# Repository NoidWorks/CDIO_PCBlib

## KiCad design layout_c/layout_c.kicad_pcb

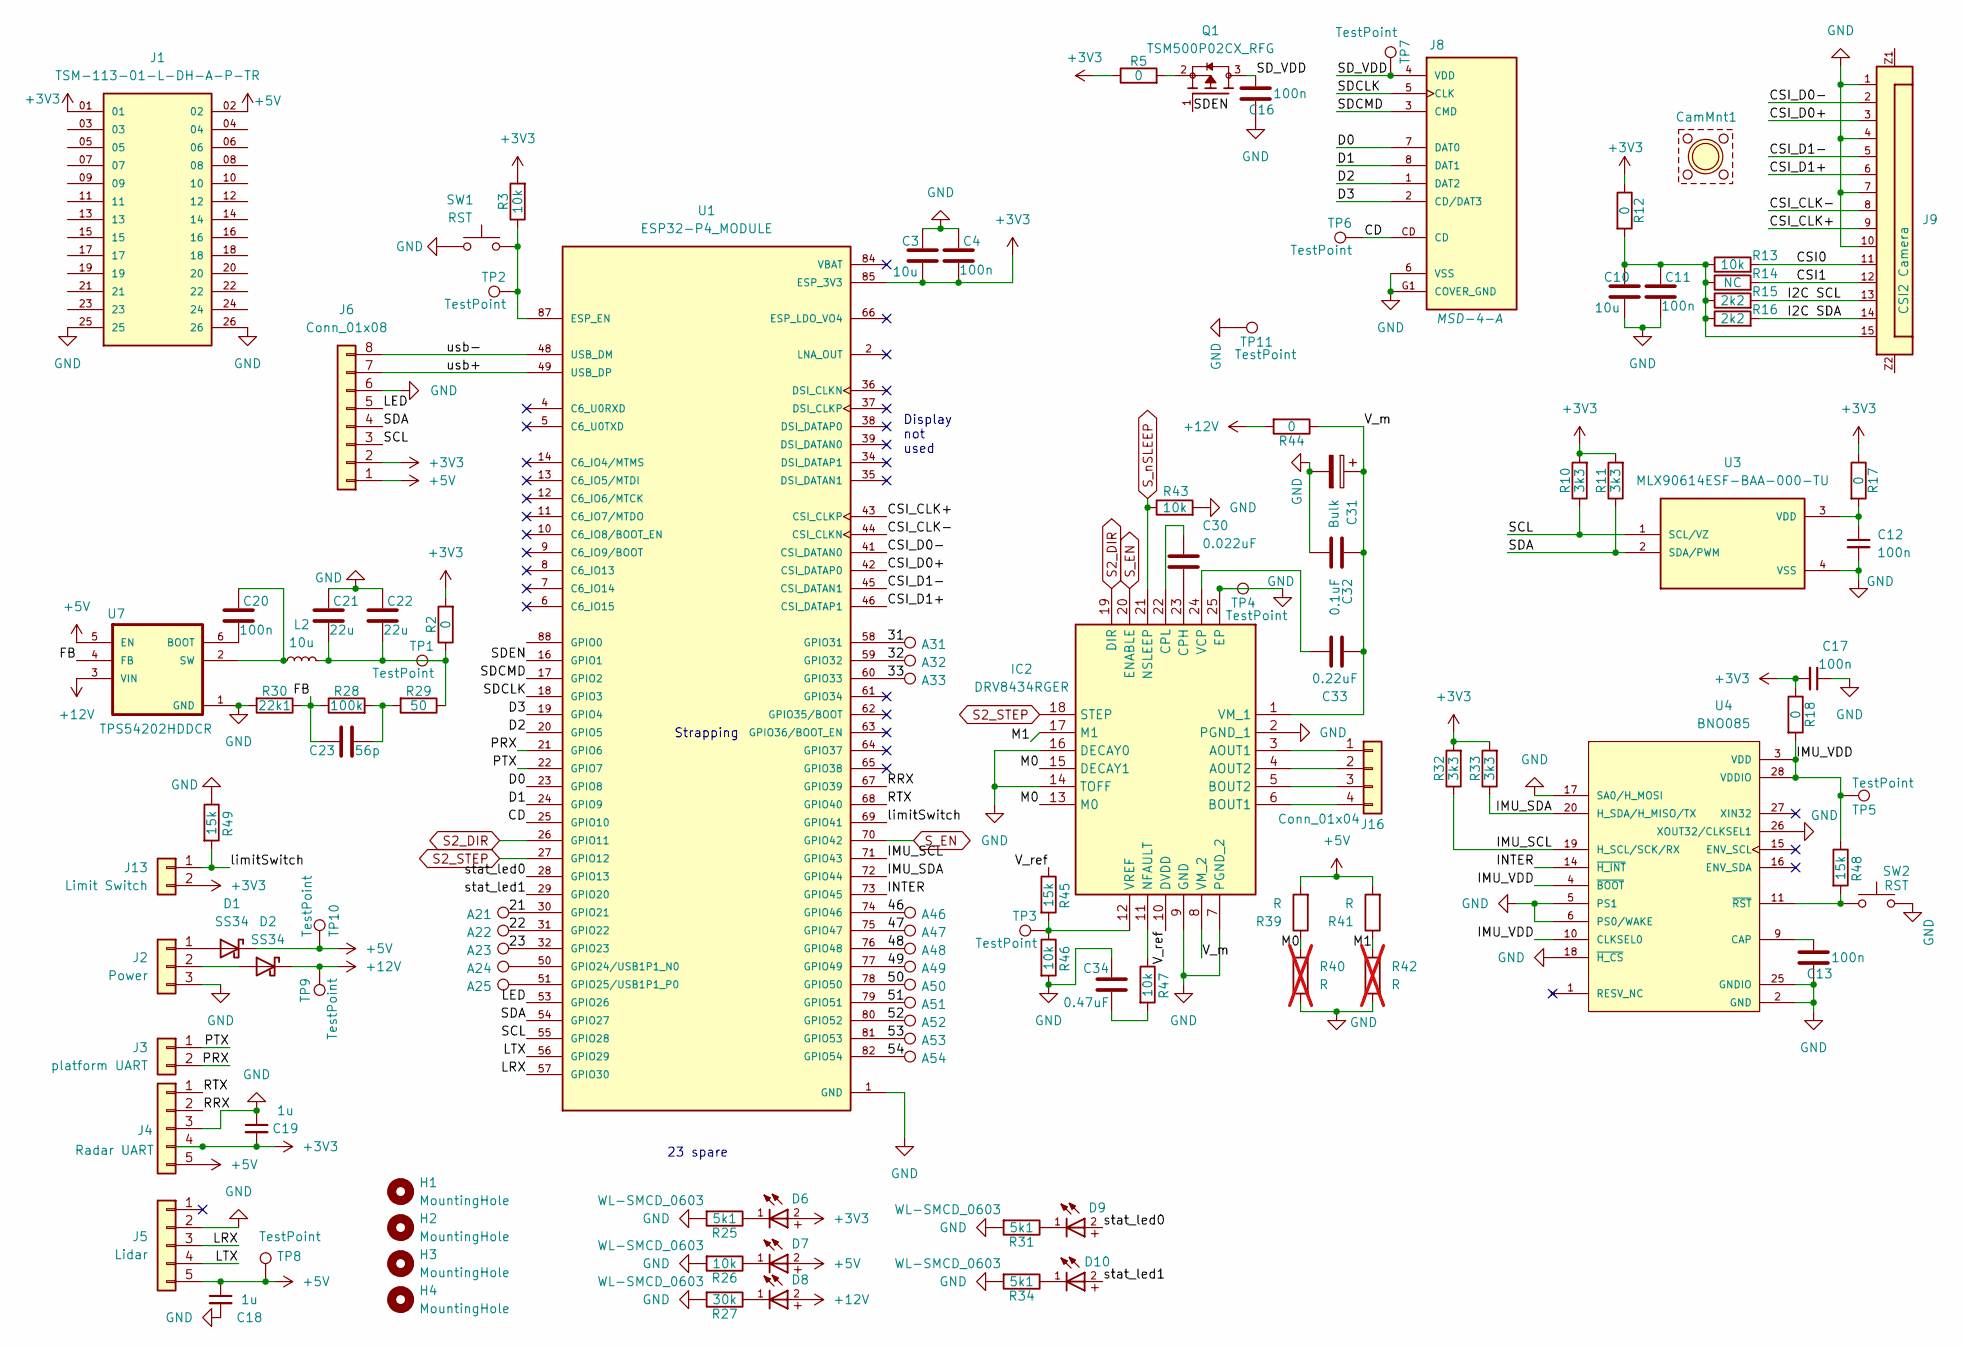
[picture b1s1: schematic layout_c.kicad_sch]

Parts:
A21, A22, A23, A24, A25, A31, A32, A33, A46, A47, A48, A49, A50, A51, A52, A53, A54: Access; TestPoint_Pad_1.5x1.5mm
C3, C10: 10u; C_0805_2012Metric
C4, C11, C12, C13, C16, C17, C20: 100n; C_0805_2012Metric
C18, C19: 1u; C_0805_2012Metric
C21, C22: 22u; C_0805_2012Metric
C23: 56p; C_0805_2012Metric
C30: 0.022uF; C_0402_1005Metric
C31: Bulk; CP_EIA-6032-15_Kemet-U
C32: 0.1uF; C_0402_1005Metric
C33: 0.22uF; C_0402_1005Metric
C34: 0.47uF; C_0402_1005Metric
CamMnt1: PiCamIndicator
D1, D2: SS34; D_SMA
D6, D7, D8, D9, D10: WL-SMCD_0603
H1, H2, H3, H4: MountingHole; MountingHole_3.2mm_M3
IC2: DRV8434RGER; QFN50P400X400X100-25N-D; Mouser Part Number 595-DRV8434RGER
J1: TSM-113-01-L-DH-A-P-TR; SAMTEC_TSM-113-01-L-DH-A-P-TR; PARTREV R
J2: Power; JST_XH_B3B-XH-A_1x03_P2.50mm_Vertical
J3: platform UART; JST_XH_B2B-XH-A_1x02_P2.50mm_Vertical
J4: Radar UART; JST_XH_B5B-XH-A_1x05_P2.50mm_Vertical
J5: Lidar; JST_XH_B5B-XH-A_1x05_P2.50mm_Vertical
J6: Conn_01x08; JST_XH_B8B-XH-A_1x08_P2.50mm_Vertical
J8: MSD-4-A; CUI_MSD-4-A; PARTREV 1.0
J9: CSI2 Camera; 686115183522
J13: Limit Switch; JST_XH_B2B-XH-A_1x02_P2.50mm_Vertical
J16: Conn_01x04; JST_XH_B4B-XH-A_1x04_P2.50mm_Vertical
L2: 10u; L_0805_2012Metric
Q1: TSM500P02CX_RFG; TRANS_TSM500P02CX_RFG; PARTREV C1907
R2, R5, R12, R17, R18, R44: 0; R_0805_2012Metric
R3, R13: 10k; R_0805_2012Metric
R10, R11, R32, R33: 3k3; R_0805_2012Metric
R14: NC; R_0805_2012Metric
R15, R16: 2k2; R_0805_2012Metric
R25, R31, R34: 5k1; R_0603_1608Metric
R26, R43, R46, R47: 10k; R_0603_1608Metric
R27: 30k; R_0603_1608Metric
R28: 100k; R_0603_1608Metric
R29: 50; R_0603_1608Metric
R30: 22k1; R_0603_1608Metric
R39, R41: R; R_0603_1608Metric
R40, R42: R; R_0603_1608Metric; not fitted
R45, R48, R49: 15k; R_0603_1608Metric
SW1, SW2: RST; SW_SPST_CK_RS282G05A3
TP1, TP2, TP3, TP5, TP6, TP7, TP8, TP9, TP10: TestPoint; TestPoint_Pad_D1.0mm
TP4, TP11: TestPoint; TestPoint_Pad_2.5x2.5mm
U1: ESP32-P4_MODULE; XCVR_ESP32-P4_MODULE; PARTREV NA
U3: MLX90614ESF-BAA-000-TU; MLX9061_TO254P942H425-4; PARTREV 13
U4: BNO085; IC_BNO085; PARTREV v1.17
U7: TPS54202HDDCR; SOT95P280X110-6N

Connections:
+3V3: C3.2, C4.2, C17.2, C19.2, D6.2, J1.01, J4.4, J6.2, J13.2, R2.2, R3.2, R5.1, R10.2, R11.2, R12.1, R17.1, R18.1, R32.2, R33.2, U1.85 (ESP_3V3), U1.86 (ESP_3V3)
+5V: C18.1, D1.1 (K), D7.2, J1.02, J4.5, J5.5, J6.1, R39.2, R41.2, TP8.1 (1_1), TP10.1 (1_1), U7.5 (EN)
+12V: D2.1 (K), D8.2, R44.2, TP9.1 (1_1), U7.3 (VIN)
/layout_c/21: A21.1 (1_1), U1.30 (GPIO21)
/layout_c/22: A22.1 (1_1), U1.31 (GPIO22)
/layout_c/23: A23.1 (1_1), U1.32 (GPIO23)
/layout_c/31: A31.1 (1_1), U1.58 (GPIO31)
/layout_c/32: A32.1 (1_1), U1.59 (GPIO32)
/layout_c/33: A33.1 (1_1), U1.60 (GPIO33)
/layout_c/46: A46.1 (1_1), U1.74 (GPIO46)
/layout_c/47: A47.1 (1_1), U1.75 (GPIO47)
/layout_c/48: A48.1 (1_1), U1.76 (GPIO48)
/layout_c/49: A49.1 (1_1), U1.77 (GPIO49)
/layout_c/50: A50.1 (1_1), U1.78 (GPIO50)
/layout_c/51: A51.1 (1_1), U1.79 (GPIO51)
/layout_c/52: A52.1 (1_1), U1.80 (GPIO52)
/layout_c/53: A53.1 (1_1), U1.81 (GPIO53)
/layout_c/54: A54.1 (1_1), U1.82 (GPIO54)
/layout_c/CD: J8.CD, TP6.1 (1_1), U1.25 (GPIO10)
/layout_c/CSI0: J9.11, R13.2
/layout_c/CSI1: J9.12, R14.2
/layout_c/CSI_CLK+: J9.9, U1.43 (CSI_CLKP)
/layout_c/CSI_CLK-: J9.8, U1.44 (CSI_CLKN)
/layout_c/CSI_D0+: J9.3, U1.42 (CSI_DATAP0)
/layout_c/CSI_D0-: J9.2, U1.41 (CSI_DATAN0)
/layout_c/CSI_D1+: J9.6, U1.46 (CSI_DATAP1)
/layout_c/CSI_D1-: J9.5, U1.45 (CSI_DATAN1)
/layout_c/D0: J8.7 (DAT0), U1.23 (GPIO8)
/layout_c/D1: J8.8 (DAT1), U1.24 (GPIO9)
/layout_c/D2: J8.1 (DAT2), U1.20 (GPIO5)
/layout_c/D3: J8.2 (CD/DAT3), U1.19 (GPIO4)
/layout_c/FB: C23.1, R28.1, R30.1, U7.4 (FB)
/layout_c/I2C SCL: J9.13, R15.2
/layout_c/I2C SDA: J9.14, R16.2
/layout_c/IMU_SCL: R32.1, U1.71 (GPIO43), U4.19 (H_SCL/SCK/RX)
/layout_c/IMU_SDA: R33.1, U1.72 (GPIO44), U4.20 (H_SDA/H_MISO/TX)
/layout_c/IMU_VDD: R18.2, R48.1, TP5.1 (1_1), U4.3 (VDD), U4.4 (~BOOT), U4.10 (CLKSEL0), U4.28 (VDDIO)
/layout_c/INTER: U1.73 (GPIO45), U4.14 (~H_INT)
/layout_c/LED: J6.5, U1.53 (GPIO26)
/layout_c/LRX: J5.3, U1.57 (GPIO30)
/layout_c/LTX: J5.4, U1.56 (GPIO29)
/layout_c/M0: IC2.13 (M0), IC2.15 (DECAY1), R39.1, R40.1
/layout_c/M1: IC2.17 (M1), R41.1, R42.1
/layout_c/PRX: J3.2, U1.21 (GPIO6)
/layout_c/PTX: J3.1, U1.22 (GPIO7)
/layout_c/RRX: J4.2, U1.67 (GPIO39)
/layout_c/RTX: J4.1, U1.68 (GPIO40)
/layout_c/SCL: J6.3, R10.1, U1.55 (GPIO28), U3.1 (SCL/VZ)
/layout_c/SDA: J6.4, R11.1, U1.54 (GPIO27), U3.2 (SDA/PWM)
/layout_c/SDCLK: J8.5 (CLK), U1.18 (GPIO3)
/layout_c/SDCMD: J8.3 (CMD), U1.17 (GPIO2)
/layout_c/SDEN: Q1.1, U1.16 (GPIO1)
/layout_c/SD_VDD: C16.2, J8.4 (VDD), Q1.3, TP7.1 (1_1)
/layout_c/V_m: C31.1, C32.1, C33.1, IC2.1 (VM_1), IC2.8 (VM_2), R44.1
/layout_c/V_ref: IC2.10 (DVDD), R45.1
/layout_c/limitSwitch: J13.1, R49.2, U1.69 (GPIO41)
/layout_c/stat_led0: D9.2, U1.28 (GPIO13)
/layout_c/stat_led1: D10.2, U1.29 (GPIO20)
/layout_c/usb+: J6.7, U1.49 (USB_DP)
/layout_c/usb-: J6.8, U1.48 (USB_DM)
GND: C3.1, C4.1, C10.2, C11.2, C12.2, C13.1, C16.1, C17.1, C18.2, C19.1, C21.1, C22.1, C31.2, C32.2, C34.1, IC2.2 (PGND_1), IC2.7 (PGND_2), IC2.9 (GND), IC2.14 (TOFF), IC2.16 (DECAY0), IC2.25 (EP), J1.25, J1.26, J2.3, J4.3, J5.2, J6.6, J8.6 (VSS), J8.G1 (COVER_GND), J8.G2 (COVER_GND), J8.G3 (COVER_GND), J8.G4 (COVER_GND), J9.1, J9.4, J9.7, J9.10, R25.2, R26.2, R27.2, R30.2, R31.2, R34.2, R40.2, R42.2, R43.2, R46.2, R49.1, SW1.1, SW2.2, TP4.1 (1_1), TP11.1 (1_1), U1.1 (GND), U1.3 (GND), U1.15 (GND), U1.33 (GND), U1.40 (GND), U1.47 (GND), U1.52 (GND), U1.83 (GND), U3.4 (VSS), U4.2 (GND), U4.5 (PS1), U4.6 (PS0/WAKE), U4.17 (SA0/H_MOSI), U4.18 (~H_CS), U4.25 (GNDIO), U4.26 (XOUT32/CLKSEL1), U7.1 (GND); also elsewhere on the board
unnamed: C10.1, C11.1, J9.15, R12.2, R13.1, R14.1, R15.1, R16.1
unnamed: C21.2, C22.2, L2.2, R2.1, R29.1, TP1.1 (1_1)
unnamed: C23.2, R28.2, R29.2
unnamed: C34.2, R47.2
unnamed: D1.2 (A), J2.1
unnamed: D2.2 (A), J2.2
unnamed: D6.1, R25.1
unnamed: D7.1, R26.1
unnamed: D8.1, R27.1
unnamed: D9.1, R31.1
unnamed: D10.1, R34.1
unnamed: IC2.3 (AOUT1), J16.1
unnamed: IC2.4 (AOUT2), J16.2
unnamed: IC2.6 (BOUT1), J16.4
unnamed: IC2.5 (BOUT2), J16.3
unnamed: C30.2, IC2.23 (CPH)
unnamed: C30.1, IC2.22 (CPL)
unnamed: IC2.11 (NFAULT), R47.1
unnamed: C33.2, IC2.24 (VCP)
unnamed: IC2.12 (VREF), R45.2, R46.1, TP3.1 (1_1)
unnamed: Q1.2, R5.2
unnamed: R3.1, SW1.2, TP2.1 (1_1), U1.87 (ESP_EN)
unnamed: A24.1 (1_1), U1.50 (GPIO24/USB1P1_N0)
unnamed: A25.1 (1_1), U1.51 (GPIO25/USB1P1_P0)
unnamed: C12.1, R17.2, U3.3 (VDD)
unnamed: C13.2, U4.9 (CAP)
unnamed: R48.2, SW2.1, U4.11 (~RST)
unnamed: C20.2, U7.6 (BOOT)
unnamed: C20.1, L2.1, U7.2 (SW)
S2_DIR: IC2.19 (DIR), U1.26 (GPIO11)
S2_STEP: IC2.18 (STEP), U1.27 (GPIO12)
S_EN: IC2.20 (ENABLE), U1.70 (GPIO42)
S_nSLEEP: IC2.21 (NSLEEP), R43.1

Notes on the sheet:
Display not used
23 spare
Strapping

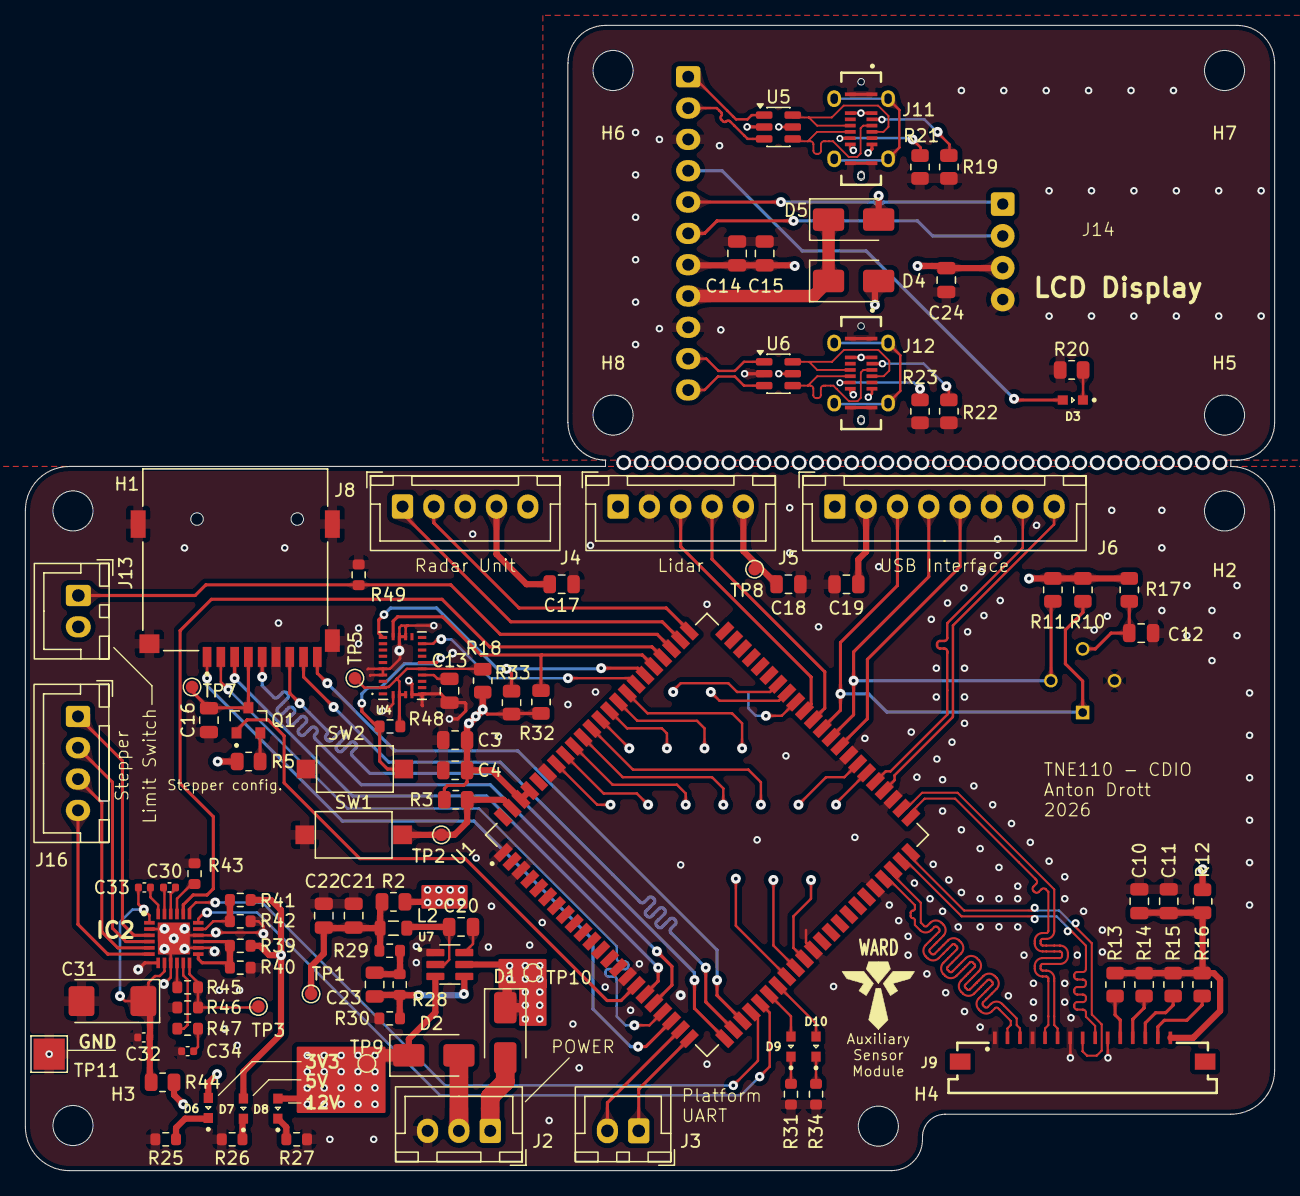
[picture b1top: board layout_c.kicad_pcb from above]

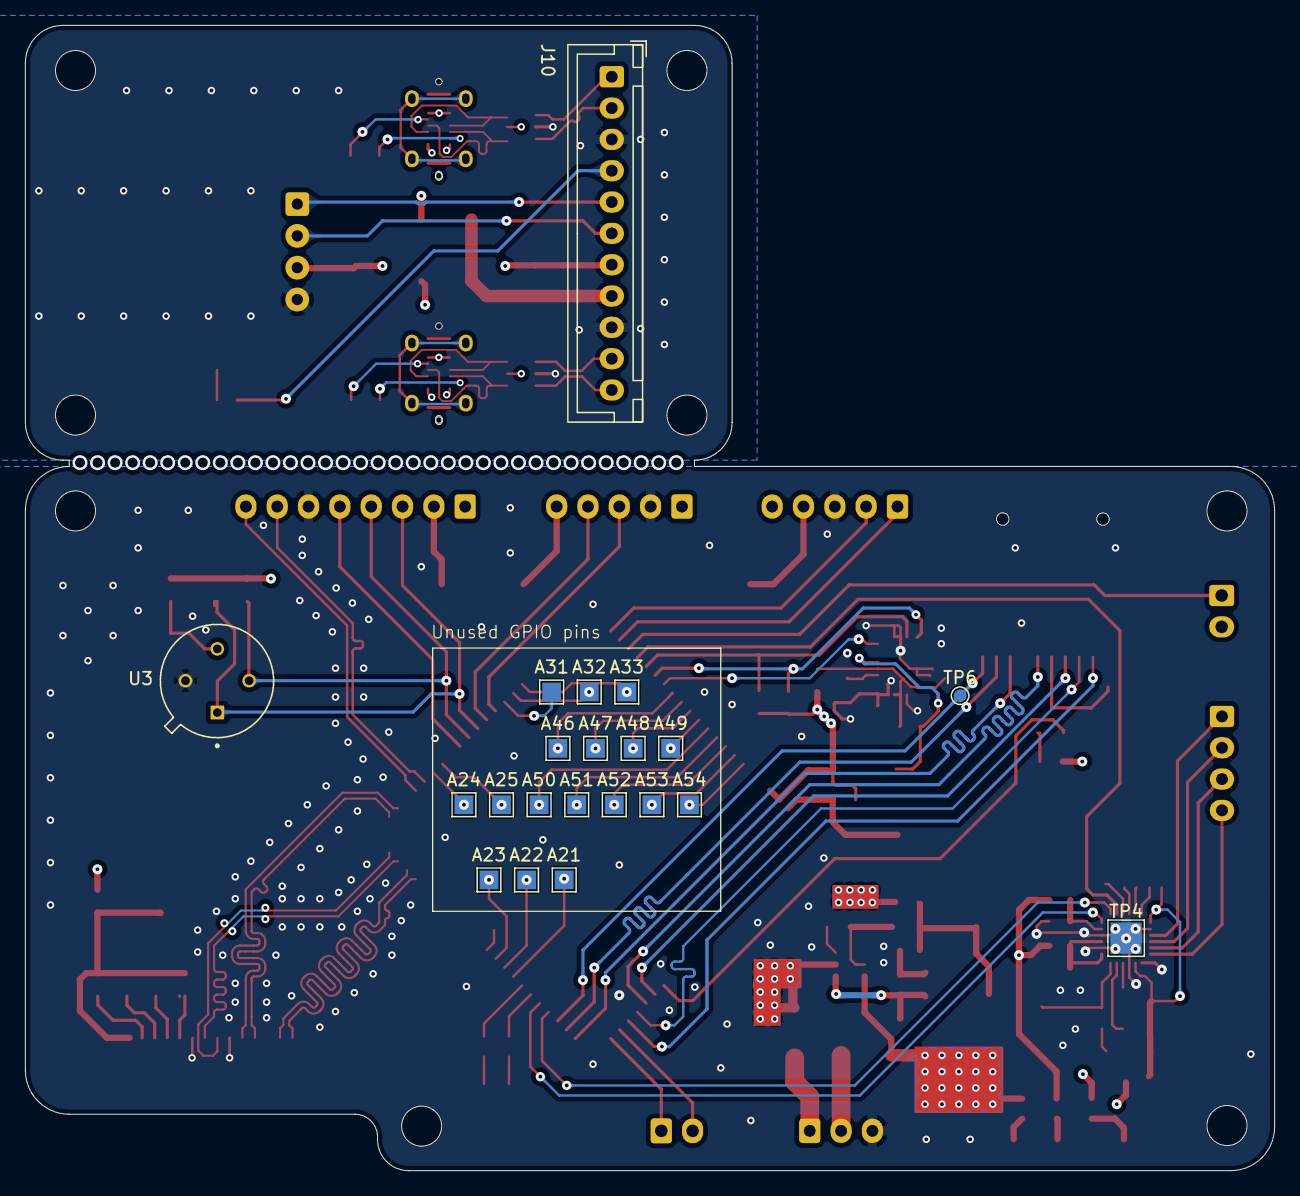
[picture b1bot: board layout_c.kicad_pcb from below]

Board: 4 copper layers, 99.7 x 91.4 mm, 130 parts (21 on the bottom side), 115 nets.

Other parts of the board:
C14, C24: 10u; C_0805_2012Metric
C15: 100n; C_0805_2012Metric
D3: WL-SMCD_0603
D4, D5: SS34; D_SMA
H5, H6, H7, H8: MountingHole; MountingHole_3.2mm_M3
J10: Conn_01x11; JST_XH_B11B-XH-A_1x11_P2.50mm_Vertical
J11, J12: USB4120-03-C_REVA6; GCT_USB4120-03-C_REVA6
J14: Conn_01x04; i2c-LCD
R19, R20, R21, R22, R23: 5k1; R_0805_2012Metric
U5, U6: USBLC6-2SC6; SOT-23-6

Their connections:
/IO plate/D1+: J10.2, U5.3 (I/O2)
/IO plate/D1-: J10.1, U5.1 (I/O1)
/IO plate/D2+: J10.11, U6.3 (I/O2)
/IO plate/D2-: J10.10, U6.1 (I/O1)
/IO plate/IO_3V3: C14.1, C15.1, C24.1, J10.7, J14.3
/IO plate/IO_5V: D4.1 (K), D5.1 (K), J10.8
/IO plate/IO_LED: D3.2, J10.4
/IO plate/IO_SCL: J10.6, J14.2
/IO plate/IO_SDA: J10.5, J14.1
/IO plate/d1+: J11.A6 (D1+), J11.B6 (D2+), U5.4 (I/O2)
/IO plate/d1-: J11.A7 (D1-), J11.B7 (D2-), U5.6 (I/O1)
/IO plate/d2+: J12.A6 (D1+), J12.B6 (D2+), U6.4 (I/O2)
/IO plate/d2-: J12.A7 (D1-), J12.B7 (D2-), U6.6 (I/O1)
GND: C14.2, C15.2, C24.2, J10.3, J10.9, J11.A1 (GND_A), J11.A12 (GND_A), J11.B1 (GND_B), J11.B12 (GND_B), J12.A1 (GND_A), J12.A12 (GND_A), J12.B1 (GND_B), J12.B12 (GND_B), J14.4, R19.1, R20.1, R21.2, R22.1, R23.2, U5.2 (GND), U6.2 (GND); also elsewhere on the board
unnamed: D3.1, R20.2
unnamed: J11.A5 (CC1), R19.2
unnamed: J11.B5 (CC2), R21.1
unnamed: J11.S1 (SHIELD), J11.S2 (SHIELD), J11.S3 (SHIELD), J11.S4 (SHIELD)
unnamed: J12.A5 (CC1), R22.2
unnamed: J12.B5 (CC2), R23.1
unnamed: J12.S1 (SHIELD), J12.S2 (SHIELD), J12.S3 (SHIELD), J12.S4 (SHIELD)
VBUS1: D4.2 (A), D5.2 (A), J11.A4 (VBUS_A), J11.A9 (VBUS_A), J11.B4 (VBUS_B), J11.B9 (VBUS_B), J12.A4 (VBUS_A), J12.A9 (VBUS_A), J12.B4 (VBUS_B), J12.B9 (VBUS_B), U5.5 (VBUS), U6.5 (VBUS)

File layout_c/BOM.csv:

"Reference","Qty","Value","Exclude from BOM","Footprint","Package","SnapEDA_Link"
"C30","1","0.022uF","","Capacitor_SMD:C_0402_1005Metric","",""
"C32","1","0.1uF","","Capacitor_SMD:C_0402_1005Metric","",""
"C33","1","0.22uF","","Capacitor_SMD:C_0402_1005Metric","",""
"C34","1","0.47uF","","Capacitor_SMD:C_0402_1005Metric","",""
"C3,C10,C14,C24","4","10u","","Capacitor_SMD:C_0805_2012Metric","",""
"C4,C11,C12,C13,C15,C16,C17,C20","8","100n","","Capacitor_SMD:C_0805_2012Metric","",""
"C18,C19","2","1u","","Capacitor_SMD:C_0805_2012Metric","",""
"C21,C22","2","22u","","Capacitor_SMD:C_0805_2012Metric","",""
"C23","1","56p","","Capacitor_SMD:C_0805_2012Metric","",""
"C31","1","Bulk","","Capacitor_Tantalum_SMD:CP_EIA-6032-15_Kemet-U","",""
"J10","1","Conn_01x11","","Connector_JST:JST_XH_B11B-XH-A_1x11_P2.50mm_Vertical","",""
"J3","1","platform UART","","Connector_JST:JST_XH_B2B-XH-A_1x02_P2.50mm_Vertical","",""
"J13","1","Limit Switch","","Connector_JST:JST_XH_B2B-XH-A_1x02_P2.50mm_Vertical","",""
"J2","1","Power","","Connector_JST:JST_XH_B3B-XH-A_1x03_P2.50mm_Vertical","",""
"J16","1","Conn_01x04","","Connector_JST:JST_XH_B4B-XH-A_1x04_P2.50mm_Vertical","",""
"J4","1","Radar UART","","Connector_JST:JST_XH_B5B-XH-A_1x05_P2.50mm_Vertical","",""
"J5","1","Lidar","","Connector_JST:JST_XH_B5B-XH-A_1x05_P2.50mm_Vertical","",""
"J6","1","Conn_01x08","","Connector_JST:JST_XH_B8B-XH-A_1x08_P2.50mm_Vertical","",""
"L2","1","10u","","Inductor_SMD:L_0805_2012Metric","",""
"J11,J12","2","USB4120-03-C_REVA6","","Library:GCT_USB4120-03-C_REVA6","None","https://www.snapeda.com/parts/USB4120-03-C/Global+Connector+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"
"U3","1","MLX90614ESF-BAA-000-TU","","Library:MLX9061_TO254P942H425-4","TO-39-4 Melexis","https://www.snapeda.com/parts/MLX90614ESF-BAA-000-TU/Melexis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"
"U7","1","TPS54202HDDCR","","Library:SOT95P280X110-6N","SOT-23-THN-6 Texas Instruments","https://www.snapeda.com/parts/TPS54202HDDCR/Texas+Instrument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"
"Q1","1","TSM500P02CX_RFG","","Library:TRANS_TSM500P02CX_RFG","SOT-23-3 Taiwan Semiconductor","https://www.snapeda.com/parts/TSM500P02CX%20RFG/taiwan/view-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"
"D3,D6,D7,D8,D9,D10","6","WL-SMCD_0603","","Library:WL-SMCD_0603","0603 Wurth Elektronik","https://www.snapeda.com/parts/150060BS55040/W%25C3%25BCrth+E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"
"U1","1","ESP32-P4_MODULE","","Library:XCVR_ESP32-P4_MODULE","None","https://www.snapeda.com/parts/ESP32-P4%20Module/Waveshare+El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"
"U5,U6","2","USBLC6-2SC6","","Package_TO_SOT_SMD:SOT-23-6","",""
"R25,R31,R34","3","5k1","","Resistor_SMD:R_0603_1608Metric","",""
"R26,R43,R46,R47","4","10k","","Resistor_SMD:R_0603_1608Metric","",""
"R27","1","30k","","Resistor_SMD:R_0603_1608Metric","",""
"R28","1","100k","","Resistor_SMD:R_0603_1608Metric","",""
"R29","1","50","","Resistor_SMD:R_0603_1608Metric","",""
"R30","1","22k1","","Resistor_SMD:R_0603_1608Metric","",""
"R39,R41","2","R","","Resistor_SMD:R_0603_1608Metric","",""
"R40,R42","2","R","","Resistor_SMD:R_0603_1608Metric","",""
"R45,R48,R49","3","15k","","Resistor_SMD:R_0603_1608Metric","",""
"R2,R5,R12,R17,R18,R44","6","0","","Resistor_SMD:R_0805_2012Metric","",""
"R3,R13","2","10k","","Resistor_SMD:R_0805_2012Metric","",""
"R10,R11,R32,R33","4","3k3","","Resistor_SMD:R_0805_2012Metric","",""
"R14","1","NC","","Resistor_SMD:R_0805_2012Metric","",""
"R15,R16","2","2k2","","Resistor_SMD:R_0805_2012Metric","",""
"R19,R20,R21,R22,R23","5","5k1","","Resistor_SMD:R_0805_2012Metric","",""
"A21,A22,A23,A24,A25,A31,A32,A33,A46,A47,A48,A49,A50,A51,A52,A53,A54","17","Access","","TestPoint:TestPoint_Pad_1.5x1.5mm","",""
"TP4,TP11","2","TestPoint","","TestPoint:TestPoint_Pad_2.5x2.5mm","",""
"TP1,TP2,TP3,TP5,TP6,TP7,TP8,TP9,TP10","9","TestPoint","","TestPoint:TestPoint_Pad_D1.0mm","",""

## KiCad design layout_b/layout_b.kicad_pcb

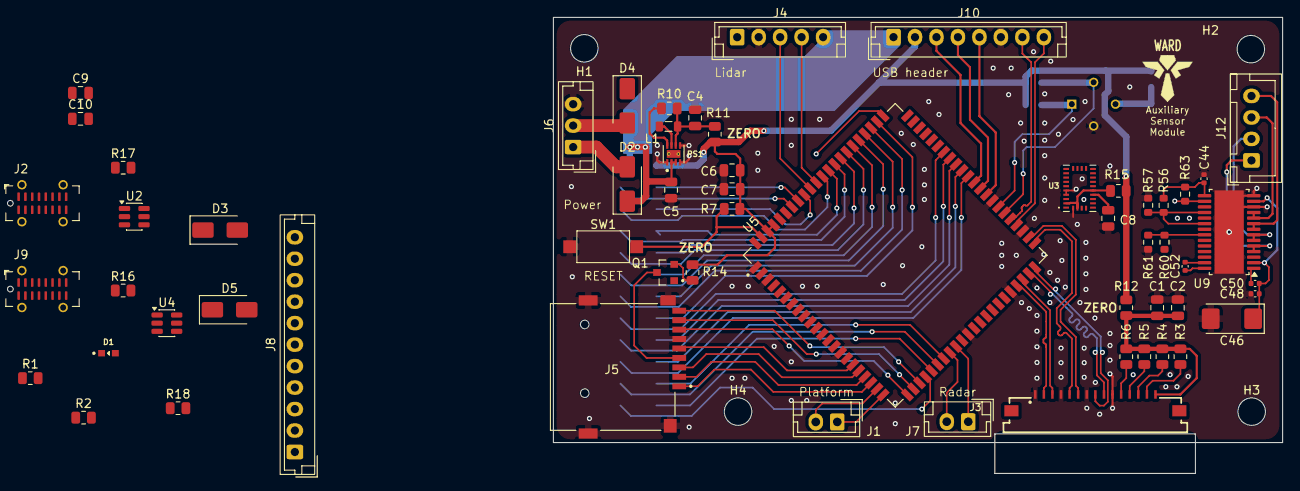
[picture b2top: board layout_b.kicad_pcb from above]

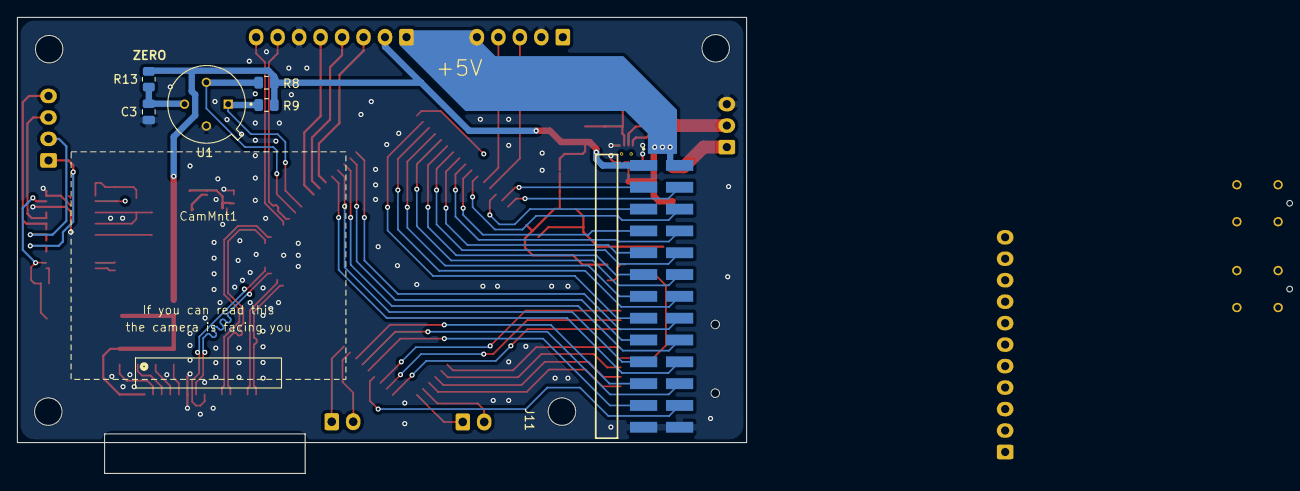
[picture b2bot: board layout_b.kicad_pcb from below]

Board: 2 copper layers, 84.9 x 53.1 mm, 74 parts (7 on the bottom side), 96 nets.

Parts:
C1, C3, C4, C7, C8, C10: 100n; C_0805_2012Metric
C2, C5, C6, C9: 10u; C_0805_2012Metric
C44: 0.47uF; C_0402_1005Metric
C46: Bulk; CP_EIA-6032-15_Kemet-U
C48: 0.1uF; C_0402_1005Metric
C50: 0.22uF; C_0402_1005Metric
C52: 0.022uF; C_0402_1005Metric
CamMnt1: PiCamIndicator
D1: WL-SMCD_0603
D2, D3, D4, D5: SS34; D_SMA
H1, H2, H3, H4, H5, H6, H7, H8: MountingHole; MountingHole_3.2mm_M3
J1: platform UART; JST_EH_B2B-EH-A_1x02_P2.50mm_Vertical
J2: USB_C_Sensors; USB_C_Receptacle_G-Switch_GT-USB-7051x
J3: CSI2 Camera; 686115183522
J4: Lidar; JST_EH_B5B-EH-A_1x05_P2.50mm_Vertical
J5: MSD-4-A; CUI_MSD-4-A
J6: Power; JST_EH_B3B-EH-A_1x03_P2.50mm_Vertical
J7: Radar UART; JST_EH_B2B-EH-A_1x02_P2.50mm_Vertical
J8: Conn_01x11; JST_EH_B11B-EH-A_1x11_P2.50mm_Vertical
J9: USB_C_Radar; USB_C_Receptacle_G-Switch_GT-USB-7051x
J10: Conn_01x08; JST_EH_B8B-EH-A_1x08_P2.50mm_Vertical
J11: TSM-113-01-L-DH-A-P-TR; SAMTEC_TSM-113-01-L-DH-A-P-TR
J12: Conn_01x04; JST_XH_B4B-XH-A_1x04_P2.50mm_Vertical
L1: 2u2; L_0805_2012Metric
PS1: TPS62162DSGT; TPS62162_SON50P200X200X80-9N
Q1: TSM500P02CX_RFG; TRANS_TSM500P02CX_RFG
R1, R2, R10, R16, R17, R18: 5k1; R_0805_2012Metric
R3, R4: 2k2; R_0805_2012Metric
R5: NC; R_0805_2012Metric
R6, R7: 10k; R_0805_2012Metric
R8, R9: 3k3; R_0805_2012Metric
R11, R12, R13, R14, R15: 0; R_0805_2012Metric
R56, R57, R60, R61: R; R_0603_1608Metric
R63: 10k; R_0603_1608Metric
SW1: RST; SW_SPST_CK_RS282G05A3
U1: MLX90614ESF-BAA-000-TU; MLX9061_TO254P942H425-4
U2, U4: USBLC6-2SC6; SOT-23-6
U3: BNO085; IC_BNO085
U5: ESP32-P4_MODULE; XCVR_ESP32-P4_MODULE
U9: DRV8434PWP; TSSOP-28-1EP_4.4x9.7mm_P0.65mm_EP3.4x9.7mm_Mask3.1x4.05mm

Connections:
+3V3: C6.2, C7.2, J10.2, J11.01, R7.2, R8.2, R9.2, R11.1, R12.1, R13.1, R14.1, R15.1, U5.85 (ESP_3V3), U5.86 (ESP_3V3)
+5V: C5.1, C44.1, D2.1 (K), J4.5, J10.1, J11.02, PS1.2 (VIN), PS1.3 (EN), R56.2, R60.2, R63.2, U9.15 (DVDD)
/IO plate/D1+: J8.2, U2.4 (I/O2)
/IO plate/D1-: J8.1, U2.6 (I/O1)
/IO plate/D2+: J8.11, U4.4 (I/O2)
/IO plate/D2-: J8.10, U4.6 (I/O1)
/IO plate/IO_3V3: C9.1, C10.1, J8.7
/IO plate/IO_5V: D3.1 (K), D5.1 (K), J8.8
/IO plate/IO_LED: D1.2, J8.4
/IO plate/d1+: J2.A6 (D+), J2.B6 (D+), U2.3 (I/O2)
/IO plate/d1-: J2.A7 (D-), J2.B7 (D-), U2.1 (I/O1)
/IO plate/d2+: J9.A6 (D+), J9.B6 (D+), U4.3 (I/O2)
/IO plate/d2-: J9.A7 (D-), J9.B7 (D-), U4.1 (I/O1)
/layout_b/11: J11.24, U5.26 (GPIO11)
/layout_b/12: J11.23, U5.27 (GPIO12)
/layout_b/13: J11.22, U5.28 (GPIO13)
/layout_b/20: J11.21, U5.29 (GPIO20)
/layout_b/29: J11.20, U5.56 (GPIO29)
/layout_b/30: J11.19, U5.57 (GPIO30)
/layout_b/31: J11.18, U5.58 (GPIO31)
/layout_b/32: J11.17, U5.59 (GPIO32)
/layout_b/33: J11.16, U5.60 (GPIO33)
/layout_b/40: J11.15, U5.68 (GPIO40)
/layout_b/41: J11.14, U5.69 (GPIO41)
/layout_b/42: J11.13, U5.70 (GPIO42)
/layout_b/43: J11.12, U5.71 (GPIO43)
/layout_b/44: J11.11, U5.72 (GPIO44)
/layout_b/45: J11.10, U5.73 (GPIO45)
/layout_b/46: J11.09, U5.74 (GPIO46)
/layout_b/47: J11.08, U5.75 (GPIO47)
/layout_b/48: J11.07, U5.76 (GPIO48)
/layout_b/49: J11.06, U5.77 (GPIO49)
/layout_b/52: J11.05, U5.80 (GPIO52)
/layout_b/53: J11.03, U5.81 (GPIO53)
/layout_b/54: J11.04, U5.82 (GPIO54)
/layout_b/CD: J5.CD, U5.25 (GPIO10)
/layout_b/CSI0: J3.11, R6.2
/layout_b/CSI1: J3.12, R5.2
/layout_b/CSI_CLK+: J3.9, U5.43 (CSI_CLKP)
/layout_b/CSI_CLK-: J3.8, U5.44 (CSI_CLKN)
/layout_b/CSI_D0+: J3.3, U5.42 (CSI_DATAP0)
/layout_b/CSI_D0-: J3.2, U5.41 (CSI_DATAN0)
/layout_b/CSI_D1+: J3.6, U5.46 (CSI_DATAP1)
/layout_b/CSI_D1-: J3.5, U5.45 (CSI_DATAN1)
/layout_b/D0: J5.7 (DAT0), U5.23 (GPIO8)
/layout_b/D1: J5.8 (DAT1), U5.24 (GPIO9)
/layout_b/D2: J5.1 (DAT2), U5.20 (GPIO5)
/layout_b/D3: J5.2 (CD/DAT3), U5.19 (GPIO4)
/layout_b/I2C SCL: J3.13, R4.2
/layout_b/I2C SDA: J3.14, R3.2
/layout_b/IMU_VDD: R15.2, U3.3 (VDD), U3.10 (CLKSEL0), U3.28 (VDDIO)
/layout_b/LED: J10.5, U5.53 (GPIO26)
/layout_b/LRX: J4.3, U5.79 (GPIO51)
/layout_b/LTX: J4.4, U5.78 (GPIO50)
/layout_b/M0: R56.1, R57.1, U9.18 (M0), U9.20 (DECAY1)
/layout_b/M1: R60.1, R61.1, U9.22 (M1)
/layout_b/PRX: J1.2, U5.21 (GPIO6)
/layout_b/PTX: J1.1, U5.22 (GPIO7)
/layout_b/RRX: J7.2, U5.30 (GPIO21)
/layout_b/RTX: J7.1, U5.31 (GPIO22)
/layout_b/SCL: J10.3, U5.55 (GPIO28)
/layout_b/SDA: J10.4, U5.54 (GPIO27)
/layout_b/SDCLK: J5.5 (CLK), U5.17 (GPIO2)
/layout_b/SDCMD: J5.3 (CMD), U5.18 (GPIO3)
/layout_b/SD_VDD: J5.4 (VDD), Q1.3
/layout_b/TEMP_SCL: R9.1, U1.1 (SCL/VZ), U5.51 (GPIO25/USB1P1_P0)
/layout_b/TEMP_SDA: R8.1, U1.2 (SDA/PWM), U5.50 (GPIO24/USB1P1_N0)
/layout_b/V_m: C46.1, C48.1, C50.1, U9.2 (VM), U9.13 (VM)
/layout_b/usb+: J10.7, U5.49 (USB_DP)
/layout_b/usb-: J10.8, U5.48 (USB_DM)
GND: C1.2, C2.2, C3.2, C4.2, C5.2, C6.1, C7.1, C8.1, C9.2, C10.2, C44.2, C46.2, C48.2, J2.A1 (GND), J2.A12 (GND), J2.B1 (GND), J2.B12 (GND), J3.1, J3.4, J3.7, J3.10, J4.2, J5.6 (VSS), J5.G1 (COVER_GND), J5.G2 (COVER_GND), J5.G3 (COVER_GND), J5.G4 (COVER_GND), J6.3, J8.3, J8.9, J9.A1 (GND), J9.A12 (GND), J9.B1 (GND), J9.B12 (GND), J10.6, J11.25, J11.26, PS1.1 (PGND), PS1.4 (AGND), PS1.5 (FB), R1.2, R2.2, R16.2, R17.2, R18.1, R57.2, R61.2, SW1.1, U1.4 (VSS), U2.2 (GND), U3.2 (GND), U3.25 (GNDIO), U3.26 (XOUT32/CLKSEL1), U4.2 (GND), U5.1 (GND), U5.3 (GND), U5.15 (GND), U5.33 (GND), U5.40 (GND), U5.47 (GND), U5.52 (GND), U5.83 (GND), U9.3 (PGND), U9.12 (PGND), U9.14 (GND), U9.19 (TOFF), U9.21 (DECAY0), U9.29 (PAD)
unnamed: C1.1, C2.1, J3.15, R3.1, R4.1, R5.1, R6.1, R12.2
unnamed: D1.1, R18.2
unnamed: D2.2 (A), J6.1
unnamed: D4.2 (A), J6.2
unnamed: J2.A5 (CC1), R1.1
unnamed: J2.B5 (CC2), R2.1
unnamed: J9.A5 (CC1), R16.1
unnamed: J9.B5 (CC2), R17.1
unnamed: J12.1, U9.4 (AOUT1), U9.5 (AOUT1)
unnamed: J12.2, U9.6 (AOUT2), U9.7 (AOUT2)
unnamed: J12.3, U9.10 (BOUT1), U9.11 (BOUT1)
unnamed: J12.4, U9.8 (BOUT2), U9.9 (BOUT2)
unnamed: PS1.8 (PG), R10.1
unnamed: L1.1, PS1.7 (SW)
unnamed: C4.1, L1.2, PS1.6 (VOS), R10.2, R11.2
unnamed: Q1.2, R14.2
unnamed: C3.1, R13.2, U1.3 (VDD)
unnamed: C8.2, U3.9 (CAP)
unnamed: R7.1, SW1.2, U5.87 (ESP_EN)
unnamed: C52.1, U9.28 (CPH)
unnamed: C52.2, U9.27 (CPL)
unnamed: C50.2, U9.1 (VCP)
unnamed: R63.1, U9.16 (~FAULT)
VBUS1: D3.2 (A), J2.A4 (VBUS), J2.A9 (VBUS), J2.B4 (VBUS), J2.B9 (VBUS), U2.5 (VBUS)
VBUS2: D5.2 (A), J9.A4 (VBUS), J9.A9 (VBUS), J9.B4 (VBUS), J9.B9 (VBUS), U4.5 (VBUS)

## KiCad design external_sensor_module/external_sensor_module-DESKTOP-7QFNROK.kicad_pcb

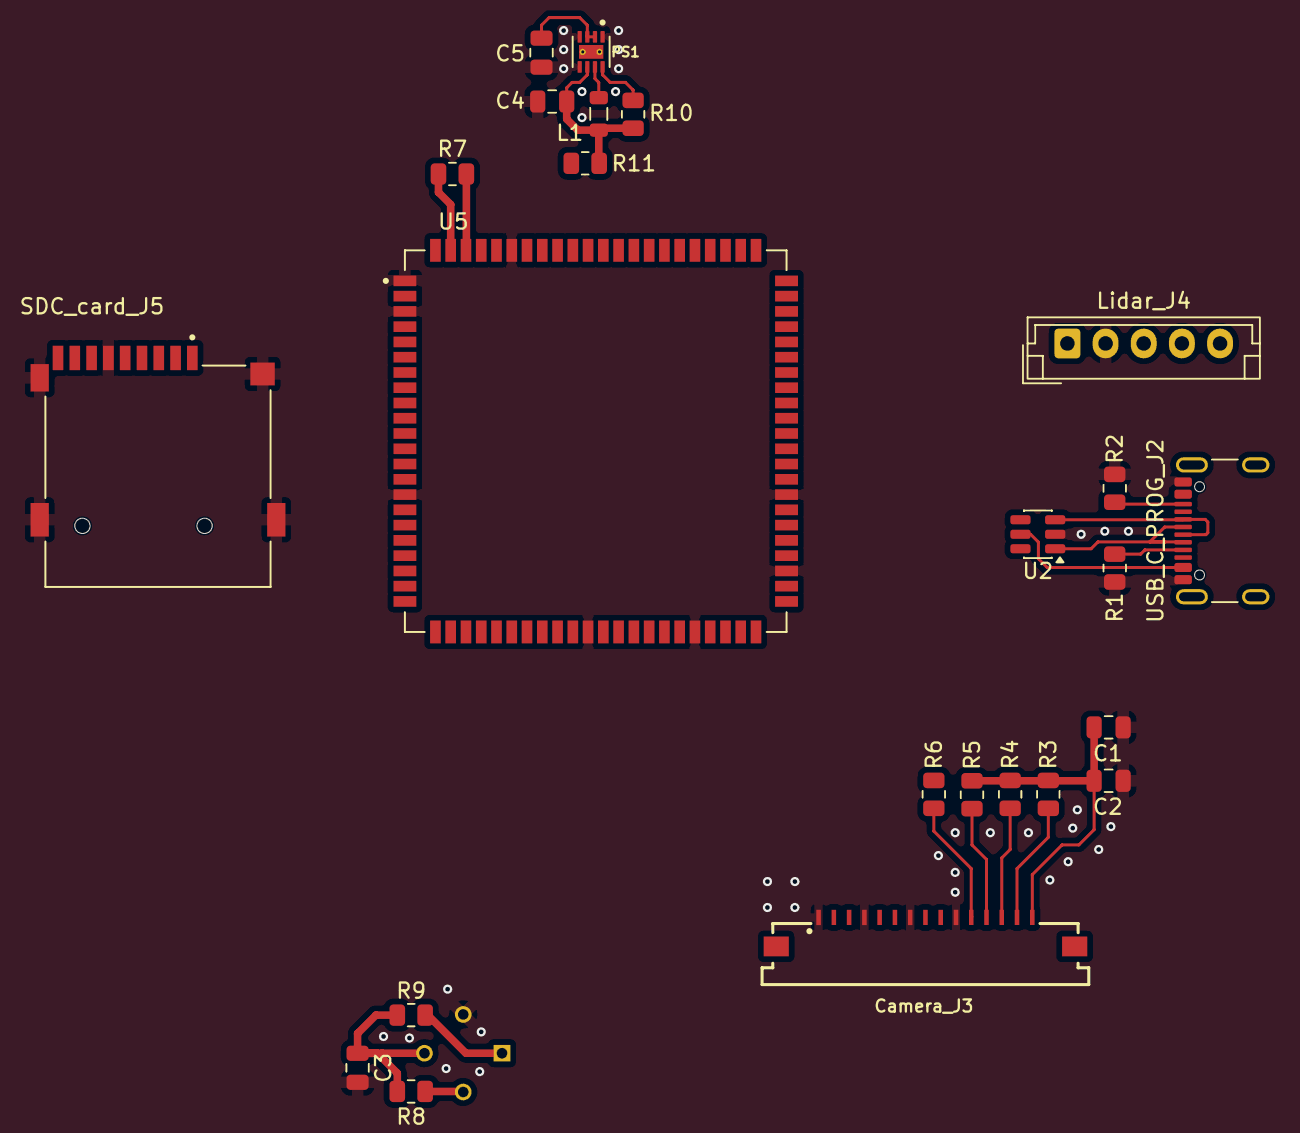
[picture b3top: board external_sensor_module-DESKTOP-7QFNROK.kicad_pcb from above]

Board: 2 copper layers, 25 parts (1 on the bottom side), 27 nets.

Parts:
C1, C3, C4: 100n; C_0805_2012Metric
C2, C5: 10u; C_0805_2012Metric
Camera_J3: 6861XX183522_686115183522; 686115183522
L1: 2u2; L_0805_2012Metric
Lidar_J4: Conn_01x05; JST_EH_B5B-EH-A_1x05_P2.50mm_Vertical
PS1: TPS62162DSGT; TPS62162_SON50P200X200X80-9N
R1, R2, R10: 5k1; R_0805_2012Metric
R3, R4: 2k2; R_0805_2012Metric
R5: NC; R_0805_2012Metric
R6, R7: 10k; R_0805_2012Metric
R8, R9: 3k3; R_0805_2012Metric
R11: 0; R_0805_2012Metric
SDC_card_J5: MSD-4-A; CUI_MSD-4-A
U1: MLX90614ESF-BAA-000-TU; MLX9061_TO254P942H425-4
U2: USBLC6-2SC6; SOT-23-6
U5: ESP32-P4_MODULE; XCVR_ESP32-P4_MODULE
USB_C_PROG_J2: USB_C_Receptacle_USB2.0_16P; USB_C_Receptacle_GCT_USB4105-xx-A_16P_TopMnt_Horizontal

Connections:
+3V3: C1.1, C2.1, C3.1, Camera_J3.15, Lidar_J4.5, R3.1, R4.1, R5.1, R6.1, R7.2, R8.2, R9.2, R11.1, SDC_card_J5.4 (VDD), U1.3 (VDD), U5.85 (ESP_3V3), U5.86 (ESP_3V3)
/CSI0: Camera_J3.11, R6.2
/CSI1: Camera_J3.12, R5.2
/CSI_CLK+: Camera_J3.9, U5.43 (CSI_CLKP)
/CSI_CLK-: Camera_J3.8, U5.44 (CSI_CLKN)
/CSI_D0+: Camera_J3.3, U5.42 (CSI_DATAP0)
/CSI_D0-: Camera_J3.2, U5.41 (CSI_DATAN0)
/CSI_D1+: Camera_J3.6, U5.46 (CSI_DATAP1)
/CSI_D1-: Camera_J3.5, U5.45 (CSI_DATAN1)
/I2C SCL: Camera_J3.13, R4.2
/I2C SDA: Camera_J3.14, R3.2
/LRX: Lidar_J4.3, U5.58 (GPIO31)
/LTX: Lidar_J4.4, U5.59 (GPIO32)
/TEMP_SCL: R9.1, U1.1 (SCL/VZ)
/TEMP_SDA: R8.1, U1.2 (SDA/PWM)
GND: C1.2, C2.2, C3.2, C4.2, C5.2, Camera_J3.1, Camera_J3.4, Camera_J3.7, Camera_J3.10, Lidar_J4.2, PS1.1 (PGND), PS1.4 (AGND), PS1.5 (FB), R1.2, R2.2, SDC_card_J5.6 (VSS), SDC_card_J5.G1 (COVER_GND), SDC_card_J5.G2 (COVER_GND), SDC_card_J5.G3 (COVER_GND), SDC_card_J5.G4 (COVER_GND), U1.4 (VSS), U2.2 (GND), U5.1 (GND), U5.3 (GND), U5.15 (GND), U5.33 (GND), U5.40 (GND), U5.47 (GND), U5.52 (GND), U5.83 (GND), USB_C_PROG_J2.A1 (GND), USB_C_PROG_J2.A12 (GND), USB_C_PROG_J2.B1 (GND), USB_C_PROG_J2.B12 (GND)
unnamed: PS1.8 (PG), R10.1
unnamed: L1.1, PS1.7 (SW)
unnamed: C4.1, L1.2, PS1.6 (VOS), R10.2, R11.2
unnamed: U2.1 (I/O1), USB_C_PROG_J2.A7 (D-), USB_C_PROG_J2.B7 (D-)
unnamed: U2.3 (I/O2), USB_C_PROG_J2.A6 (D+), USB_C_PROG_J2.B6 (D+)
unnamed: R7.1, U5.87 (ESP_EN)
unnamed: U2.6 (I/O1), U5.48 (USB_DM)
unnamed: U2.4 (I/O2), U5.49 (USB_DP)
unnamed: R1.1, USB_C_PROG_J2.A5 (CC1)
unnamed: R2.1, USB_C_PROG_J2.B5 (CC2)
VBUS: C5.1, PS1.2 (VIN), PS1.3 (EN), U2.5 (VBUS), USB_C_PROG_J2.A4 (VBUS), USB_C_PROG_J2.A9 (VBUS), USB_C_PROG_J2.B4 (VBUS), USB_C_PROG_J2.B9 (VBUS)
